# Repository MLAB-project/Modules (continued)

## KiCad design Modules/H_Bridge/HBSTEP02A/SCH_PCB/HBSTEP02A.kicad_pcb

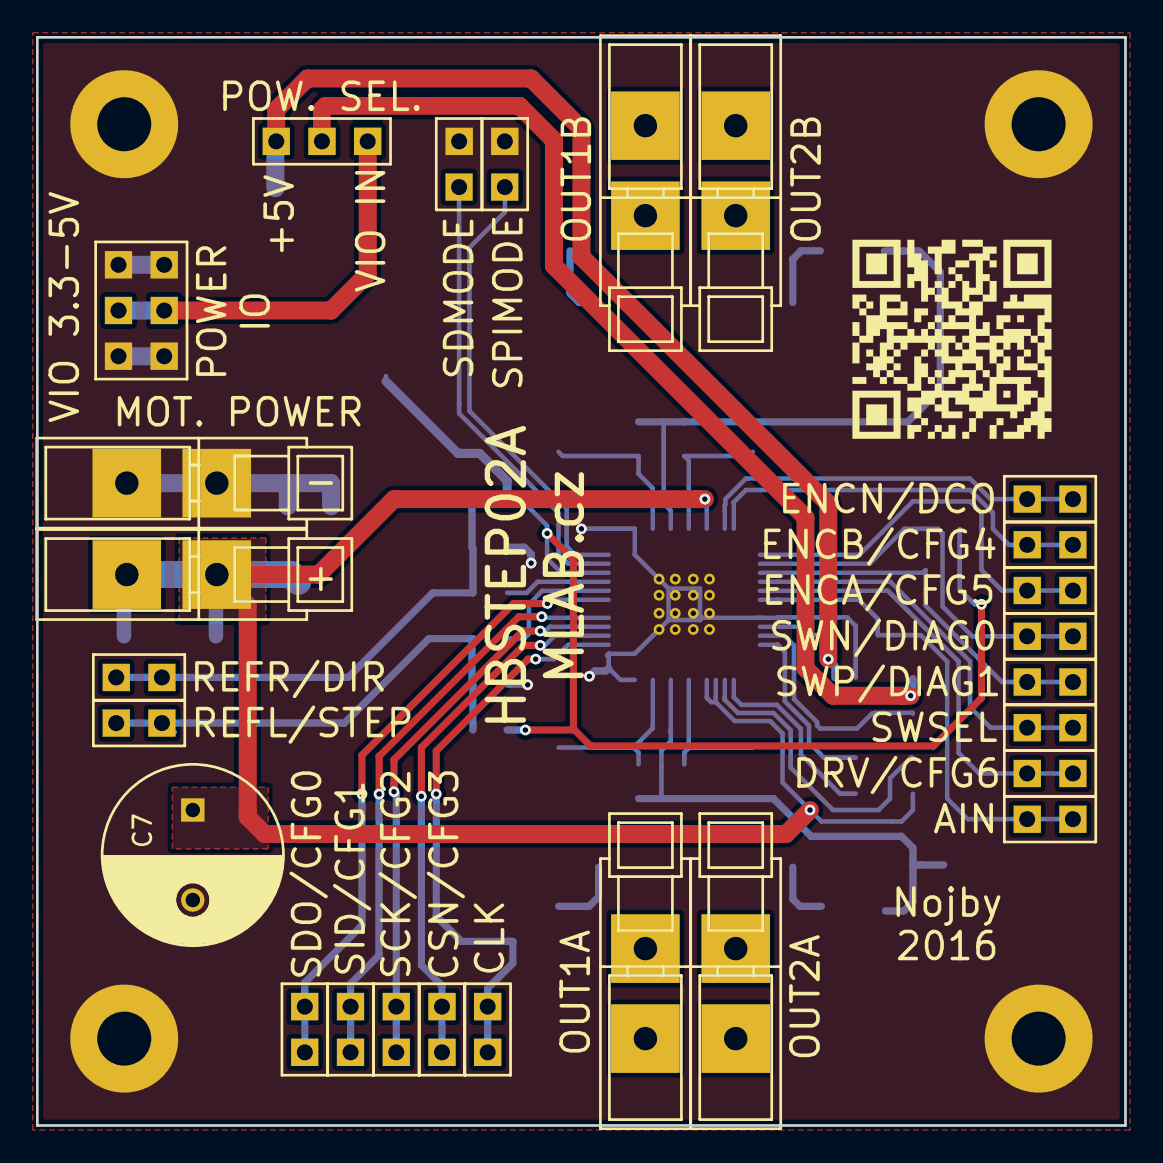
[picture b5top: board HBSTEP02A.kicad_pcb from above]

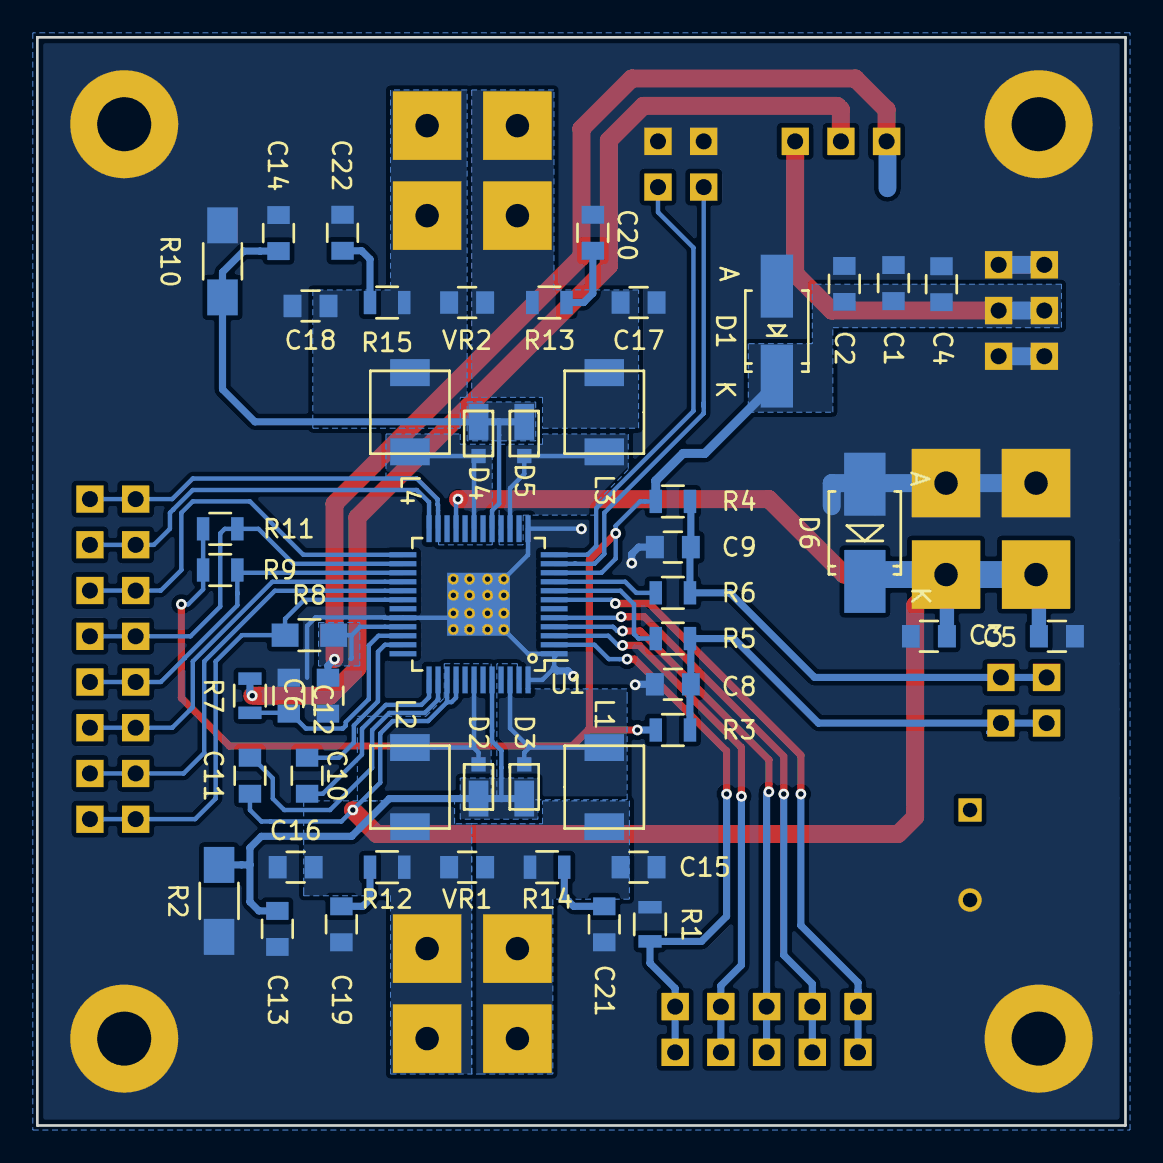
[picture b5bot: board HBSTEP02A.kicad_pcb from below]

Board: 2 copper layers, 60.5 x 60.5 mm, 79 parts (49 on the bottom side), 42 nets.

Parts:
C1, C6: 4u7; C_0805
C2, C3, C4, C5, C11, C13, C14: 100nF; C_0805
C7: 100uF/50V; C_Radial_D10_L13_P5
C8, C9: 1nF; C_0805
C10: 22n; C_0805
C12: 470nF; C_0805
C15, C16, C17, C18: 470pF; C_0805
C19, C20, C21, C22: 4n7; C_0805
D1: M4; SMA_Handsoldering
D2, D3, D4, D5: MSS1P6; SCHOT_D_MSS1P6
D6: M4; SMB_Handsoldering
J1: VIO 3.3-5V; Straight_2x03
J2: REFL/STEP; Straight_1x02
J3: REFR/DIR; Straight_1x02
J4: CLK; Straight_1x02
J5, J6, J16, J17, J24, J25: CONN1_1; WAGO256
J7: CSN/CFG3; Straight_1x02
J8: SCK/CFG2; Straight_1x02
J9: SID/CFG1; Straight_1x02
J10: SDO/CFG0; Straight_1x02
J11: ENCN/DCO; Straight_1x02
J12: ENCB/CFG4; Straight_1x02
J13: ENCA/CFG5; Straight_1x02
J14: SWP/DIAG1; Straight_1x02
J15: SWN/DIAG0; Straight_1x02
J18: POW. SEL.; Straight_1x03
J19: SDMODE; Straight_1x02
J20: DRV/CFG6; Straight_1x02
J21: SWSEL; Straight_1x02
J22: SPIMODE; Straight_1x02
J23: AIN; Straight_1x02
L1, L2, L3, L4: 100nH; Inductor_4.5_4.1
M1, M2, M3, M4: HOLE; MountingHole_3mm
R1: 1k; R_0805
R2, R10: 0R27; R_1206_HandSoldering
R3, R4, R9, R11: 10k; R_0805
R5, R6: 22k; R_0805
R7: 3.3; R_0805
R8: _R; R_0805_HandSoldering
R12, R13, R14, R15: 27; R_0805
U1: TMC5130A; TQFP-48-1EP_7x7mm_Pitch0.5mm_TRINAMIC
VR1, VR2: VR; C_0805

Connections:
+5V: C6.1, J18.1, R8.1, U1.33
GNDA: C1.2, C2.2, C3.2, C4.2, C5.2, C6.2, C7.2, C8.2, C9.2, C12.2, C13.2, C14.2, C15.1, C16.2, C17.1, C18.1, C19.2, C20.1, C21.1, C22.1, D1.2, D6.2, J1.1, J1.2, J1.5, J1.6, J6.1, J19.1, J22.1, M1.1, M2.1, M3.1, M4.1, R1.2, R2.1, R10.1, U1.1, U1.13, U1.32, U1.48, U1.49
unnamed: C8.1, J2.1, J2.2, R3.2, R5.2
unnamed: C9.1, J3.1, J3.2, R4.2, R6.2
unnamed: C10.1, U1.35
unnamed: C10.2, U1.37
unnamed: C11.1, U1.38
unnamed: C12.1, R7.2, U1.34
unnamed: C13.1, D2.2, D3.2, R2.2, U1.44
unnamed: C14.1, D4.2, D5.2, R10.2, U1.17
unnamed: C15.2, J16.1, L1.2, R14.2, VR1.1
unnamed: C16.1, J17.1, L2.2, R12.1, VR1.2
unnamed: C17.2, J24.1, L3.2, R13.2, VR2.1
unnamed: C18.2, J25.1, L4.2, R15.2, VR2.2
unnamed: C19.1, R12.2
unnamed: C20.2, R13.1
unnamed: C21.2, R14.1
unnamed: C22.2, R15.1
unnamed: D2.1, L2.1, U1.42
unnamed: D3.1, L1.1, U1.46
unnamed: D4.1, L4.1, U1.19
unnamed: D5.1, L3.1, U1.15
unnamed: J4.1, J4.2, R1.1, U1.2
unnamed: J7.1, J7.2, U1.3
unnamed: J8.1, J8.2, U1.4
unnamed: J9.1, J9.2, U1.5
unnamed: J10.1, J10.2, U1.7
unnamed: J11.1, J11.2, U1.23
unnamed: J12.1, J12.2, U1.24
unnamed: J13.1, J13.2, U1.25
unnamed: J14.1, J14.2, R9.2, U1.27
unnamed: J15.1, J15.2, R11.2, U1.26
unnamed: J19.2, U1.11
unnamed: J20.1, J20.2, U1.29
unnamed: J21.1, J21.2, U1.28
unnamed: J22.2, U1.12
unnamed: J23.1, J23.2, R8.2, U1.30
unnamed: R5.1, U1.8
unnamed: R6.1, U1.9
VCC: J18.2, R7.1
VCOM: C1.1, C2.1, C4.1, D1.1, J1.3, J1.4, J18.3, R3.1, R4.1, R9.1, R11.1, U1.10
VSS: C3.1, C5.1, C7.1, C11.2, D6.1, J5.1, U1.21, U1.39, U1.40

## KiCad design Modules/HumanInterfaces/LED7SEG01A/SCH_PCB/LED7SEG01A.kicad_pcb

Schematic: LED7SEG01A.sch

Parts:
AFF1: FYS-40011DS-11
C1: 10uF; SMD-0805
C2, C3: 47uF; TantalC_SizeC_Reflow
C4: 100nF; SMD-0805
D1: BZV55C-5,6V; MiniMELF_Standard
D2: M4; Diode-SMA_Standard
D3, D4: L-813ID; LED-10MM
J1, J27: JUMP_4X2; Straight_2x04
J5, J6, J7, J8, J9, J28, J29, J30, J31, J36: JUMP_2x1; Straight_2x01
J11, J12, J13, J14, J15, J16, J17, J18, J19, J20, J21, J22, J23, J24, J25, J26, J37, J38, J39, J40, J41, J42, J43, J44: CONN1_1; Straight_1x01
M1, M3, M5, M6, M7, M8, M9, M10: HOLE; MountingHole_3mm
R1, R2, R3, R4, R5, R6, R28, R30: 10k; SMD-0805
R7, R8, R9, R10, R11, R12, R13, R14, R25, R26, R27, R29, R31, R32: -; SMD-0805
R15, R16, R17, R18, R19, R20, R22: 150R; SMD-1206
R21: 300R; SMD-1206
R23: 0R; SMD-0805
R24: 0R; SMD-1206
U1: PCA9635PW; TSSOP28

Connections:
+12V: AFF1.1 (C.A.), AFF1.8 (C.A.), C3.1, D2.2 (K), D3.2, D4.2, J1.3 (4), J1.4, J1.5, J1.6 (5), J27.3 (4), J27.4, J27.5, J27.6 (5), J37.1, J38.1, J39.1, J40.1, J41.1, J42.1, J43.1, J44.1, R32.1
/#OE: J36.1, J36.2, R5.1, U1.23 (#OE)
/A: AFF1.7 (a), J21.1, R9.1, R17.1
/A0: R30.2, R31.1, U1.1 (A0)
/A1: R28.2, R29.1, U1.2 (A1)
/A2: R1.1, R25.2, U1.3 (A2)
/A3: R2.1, R26.2, U1.4 (A3)
/A4: R3.1, R27.2, U1.5 (A4)
/B: AFF1.6 (b), D4.1, J23.1, R11.1, R19.1
/C: AFF1.4 (c), J22.1, R10.1, R18.1
/D: AFF1.3 (d), J24.1, R12.1, R20.1
/DP: AFF1.5 (DP), J25.1, R13.1, R21.1
/E: D3.1, J26.1, R14.1, R22.1, R24.2
/F: AFF1.9 (f), J20.1, R8.1, R16.1
/G: AFF1.10 (g), J19.1, R7.1, R15.1
/LED00: J11.1, R7.2, R15.2, U1.6 (LED0)
/LED01: J12.1, R8.2, R16.2, U1.7 (LED1)
/LED02: J13.1, R9.2, R17.2, U1.8 (LED2)
/LED03: J14.1, R11.2, R19.2, U1.9 (LED3)
/LED04: J15.1, R13.2, R21.2, U1.10 (LED4)
/LED05: J16.1, R10.2, R18.2, U1.11 (LED5)
/LED06: J17.1, R12.2, R20.2, U1.12 (LED6)
/LED07: J18.1, R14.2, R22.2, U1.13 (LED7)
/SCL: J7.1, J7.2, J30.1, J30.2, R6.2, U1.26 (SCL)
/SDA: J6.1, J6.2, R4.2, R23.1, U1.27 (SDA)
GND: C1.2, C2.2, C3.2, C4.2, D1.1 (A), D2.1 (A), J1.1 (2), J1.2, J1.7 (8), J1.8, J8.1, J8.2, J9.1, J9.2, J27.1 (2), J27.2, J27.7 (8), J27.8, J31.1, J31.2, M1.1, M3.1, M5.1, M6.1, M7.1, M8.1, M9.1, M10.1, R1.2, R2.2, R3.2, R5.2, R29.2, R31.2, U1.14 (GND), U1.24 (A5), U1.25 (A6)
unnamed: AFF1.2 (e), R24.1
unnamed: J29.1, J29.2, R23.2
VDD: C1.1, C2.1, C4.1, D1.2 (K), J5.1, J5.2, J28.1, J28.2, R4.1, R6.1, R25.1, R26.1, R27.1, R28.1, R30.1, R32.2, U1.28 (VDD)

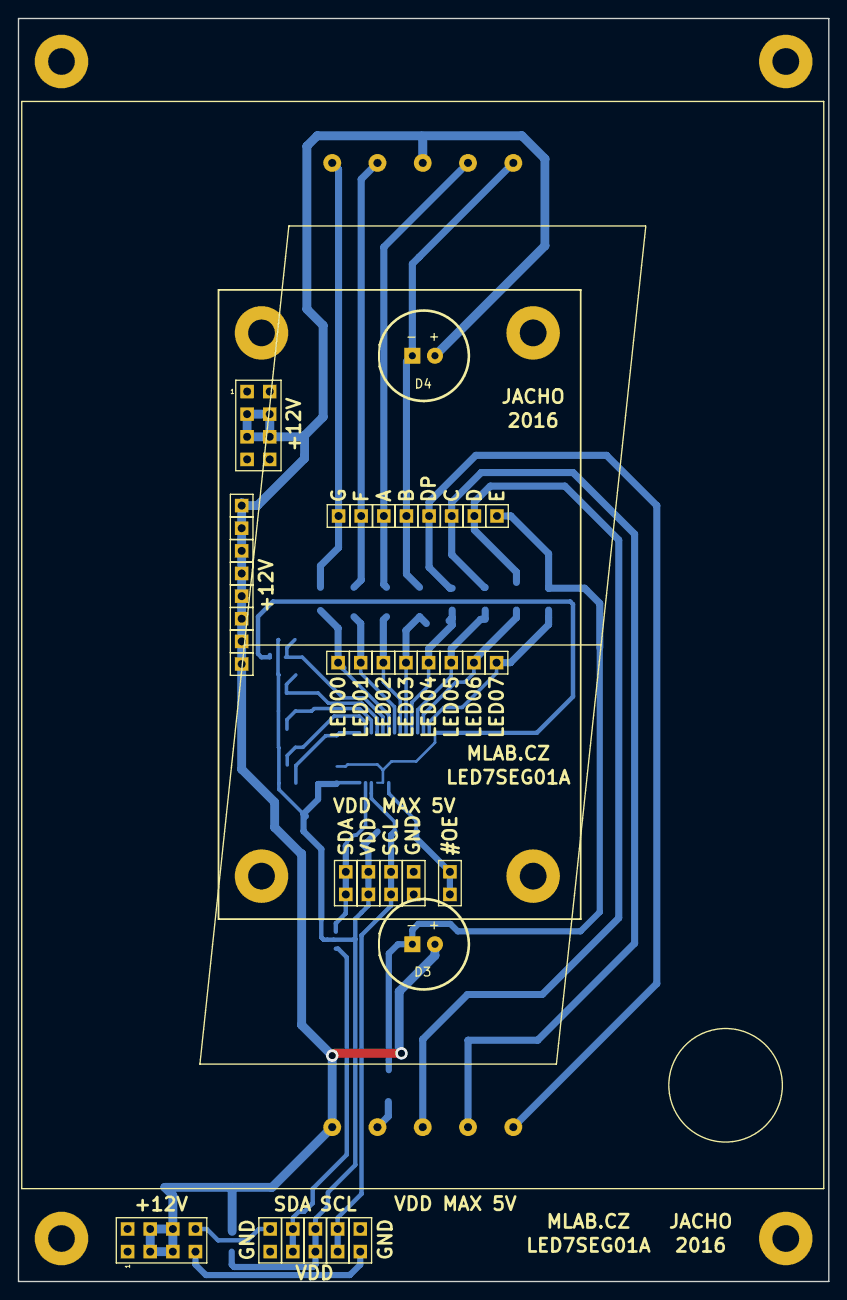
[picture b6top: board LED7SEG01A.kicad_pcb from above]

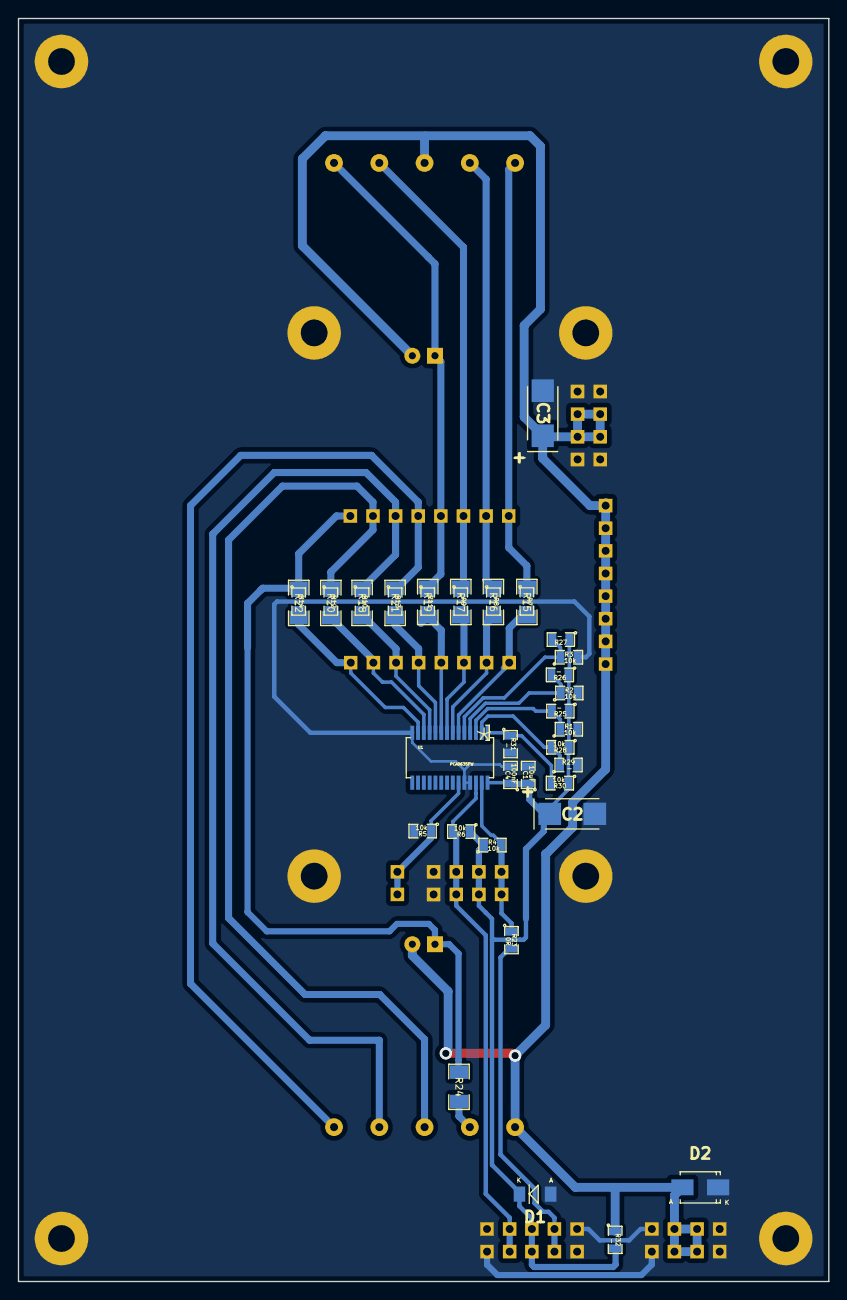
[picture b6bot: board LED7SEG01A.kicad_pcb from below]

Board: 2 copper layers, 90.9 x 141.7 mm, 86 parts (39 on the bottom side), 29 nets.

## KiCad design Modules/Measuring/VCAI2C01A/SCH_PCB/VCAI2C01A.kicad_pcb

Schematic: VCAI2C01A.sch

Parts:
C1, C4, C6, C7, C8, C9, C10, C11: C; SMD-0805
C2, C5, C12: 100nF; SMD-0805
C3: 10uF; SMD-0805
D1: BZV55C; Diode-MiniMELF_Standard
D2, D3, D4, D5, D6, D7, D8, D9: BAS85; MiniMELF_Standard
J2, J4, J6, J8: CONN_2; Straight_1x02
J3: JUMP_2x1; Straight_2x01
J5, J7, J9, J14, J15, J16, J17, J18, J19, J20, J21, J22, J23: JUMP_2x1; Straight_1x02
J10, J11: JUMP2_2x1; Straight_2x01
J13: JUMP_5X2; Straight_2x05
L1: BLM21PG300SN1D; SMD-0805
M1, M2, M3, M4: HOLE; MountingHole_3mm
R1, R2, R11, R12: 249R; SMD-1206
R3, R4, R5, R6, R13, R14, R15, R16: 180K; SMD-0805
R7, R8, R9, R10, R17, R18, R19, R20: 33K; SMD-0805
R21, R22, R23, R24: 10K; SMD-0805
U1, U2: TLC27L2ID; SOIC-8_3.9x4.9mm_Pitch1.27mm
U3: MCP3424; SOIC-14

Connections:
/A0: J10.1, R22.1, U3.9 (ADR0)
/A1: J11.1, R21.1, U3.10 (ADR1)
/IN1+: J9.1, J9.2, R1.1, R4.2
/IN1-: J2.1, J7.1, J7.2, R3.2
/IN1_2+: C1.1, D4.2 (A), R4.1, R7.2, U1.3 (+)
/IN1_2-: C6.2, D2.2 (A), R3.1, R9.1, U1.2 (-)
/IN2+: J16.1, J16.2, R2.1, R6.2
/IN2-: J4.1, J15.1, J15.2, R5.2
/IN2_2+: C4.1, D5.2 (A), R6.1, R8.2, U1.5 (+)
/IN2_2-: C7.2, D3.2 (A), R5.1, R10.1, U1.6 (-)
/IN3+: J19.1, J19.2, R11.1, R14.2
/IN3-: J6.1, J18.1, J18.2, R13.2
/IN3_2+: C8.1, D8.2 (A), R14.1, R17.2, U2.3 (+)
/IN3_2-: C10.2, D6.2 (A), R13.1, R19.1, U2.2 (-)
/IN4+: J22.1, J22.2, R12.1, R16.2
/IN4-: J8.1, J21.1, J21.2, R15.2
/IN4_2+: C9.1, D9.2 (A), R16.1, R18.2, U2.5 (+)
/IN4_2-: C11.2, D7.2 (A), R15.1, R20.1, U2.6 (-)
/OUT1: C6.1, R9.2, U1.1, U3.1 (CH1+)
/OUT2: C7.1, R10.2, U1.7, U3.3 (CH2+)
/OUT3: C10.1, R19.2, U2.1, U3.11 (CH3+)
/OUT4: C11.1, R20.2, U2.7, U3.13 (CH4+)
/SCL: J13.7, J13.8 (7), R24.2, U3.8 (SCL)
/SDA: J13.3 (4), J13.4, R23.2, U3.7 (SDA)
GND: C1.2, C2.2, C3.2, C4.2, C5.2, C8.2, C9.2, C12.2, D1.1 (K), J3.1, J3.2, J5.1, J5.2, J13.1 (2), J13.2, J13.9 (10), J13.10, J14.1, J14.2, J17.1, J17.2, J20.1, J20.2, J23.1, J23.2, M1.1, M2.1, M3.1, M4.1, R7.1, R8.1, R17.1, R18.1, R21.2, R22.2, U1.4 (GND), U2.4 (GND), U3.2 (CH1-), U3.4 (CH2-), U3.5 (VSS), U3.12 (CH3-), U3.14 (CH4-)
unnamed: C2.1, C3.1, L1.2, U3.6 (VDD)
unnamed: J2.2 (PM), R1.2
unnamed: J4.2 (PM), R2.2
unnamed: J6.2 (PM), R11.2
unnamed: J8.2 (PM), R12.2
VCC: C5.1, C12.1, D1.2 (A), D2.1 (K), D3.1 (K), D4.1 (K), D5.1 (K), D6.1 (K), D7.1 (K), D8.1 (K), D9.1 (K), J10.2, J11.2, J13.5 (6), J13.6, L1.1, R23.1, R24.1, U1.8 (VDD), U2.8 (VDD)

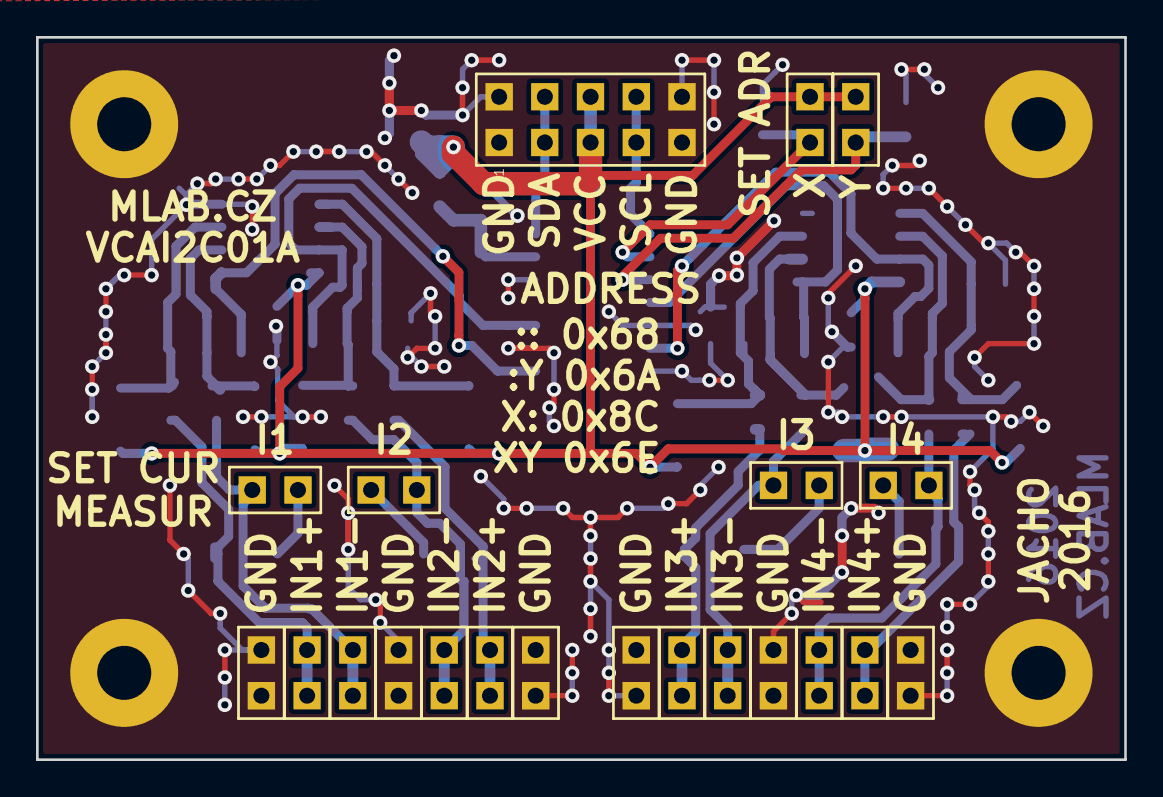
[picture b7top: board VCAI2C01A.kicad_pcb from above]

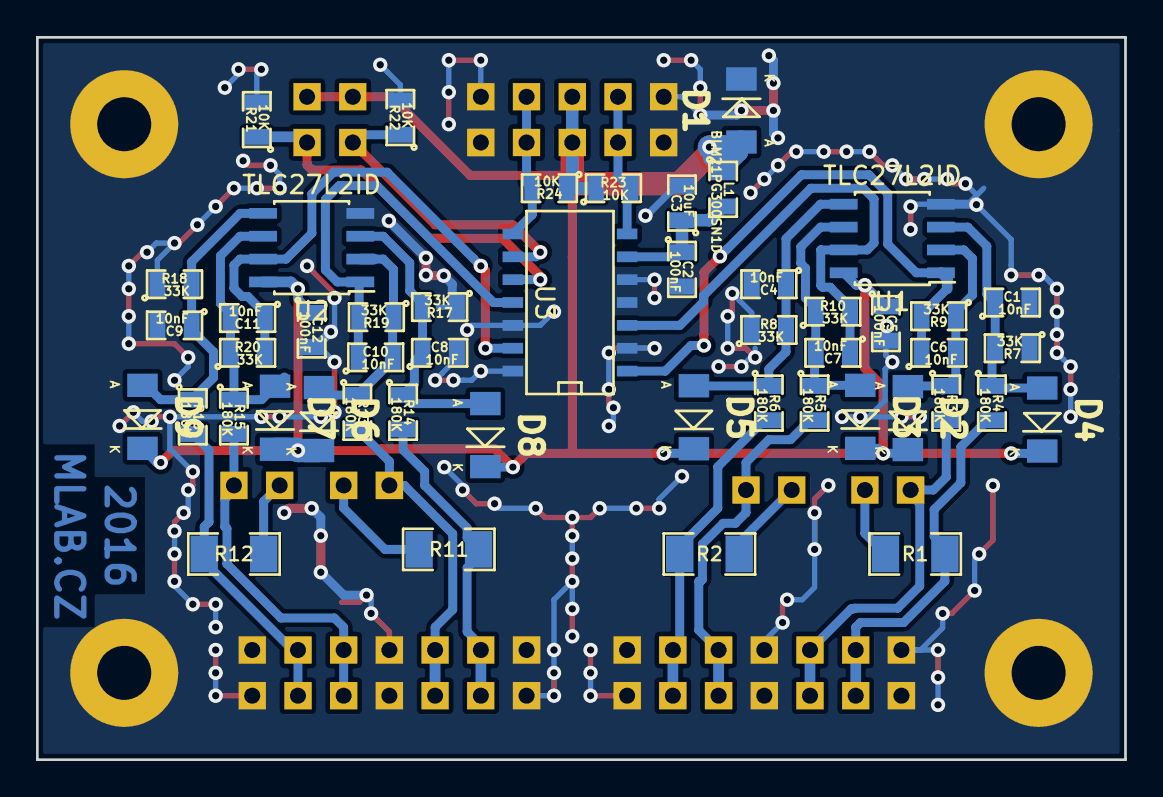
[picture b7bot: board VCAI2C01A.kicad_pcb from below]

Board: 2 copper layers, 60.5 x 40.1 mm, 74 parts (49 on the bottom side), 31 nets.

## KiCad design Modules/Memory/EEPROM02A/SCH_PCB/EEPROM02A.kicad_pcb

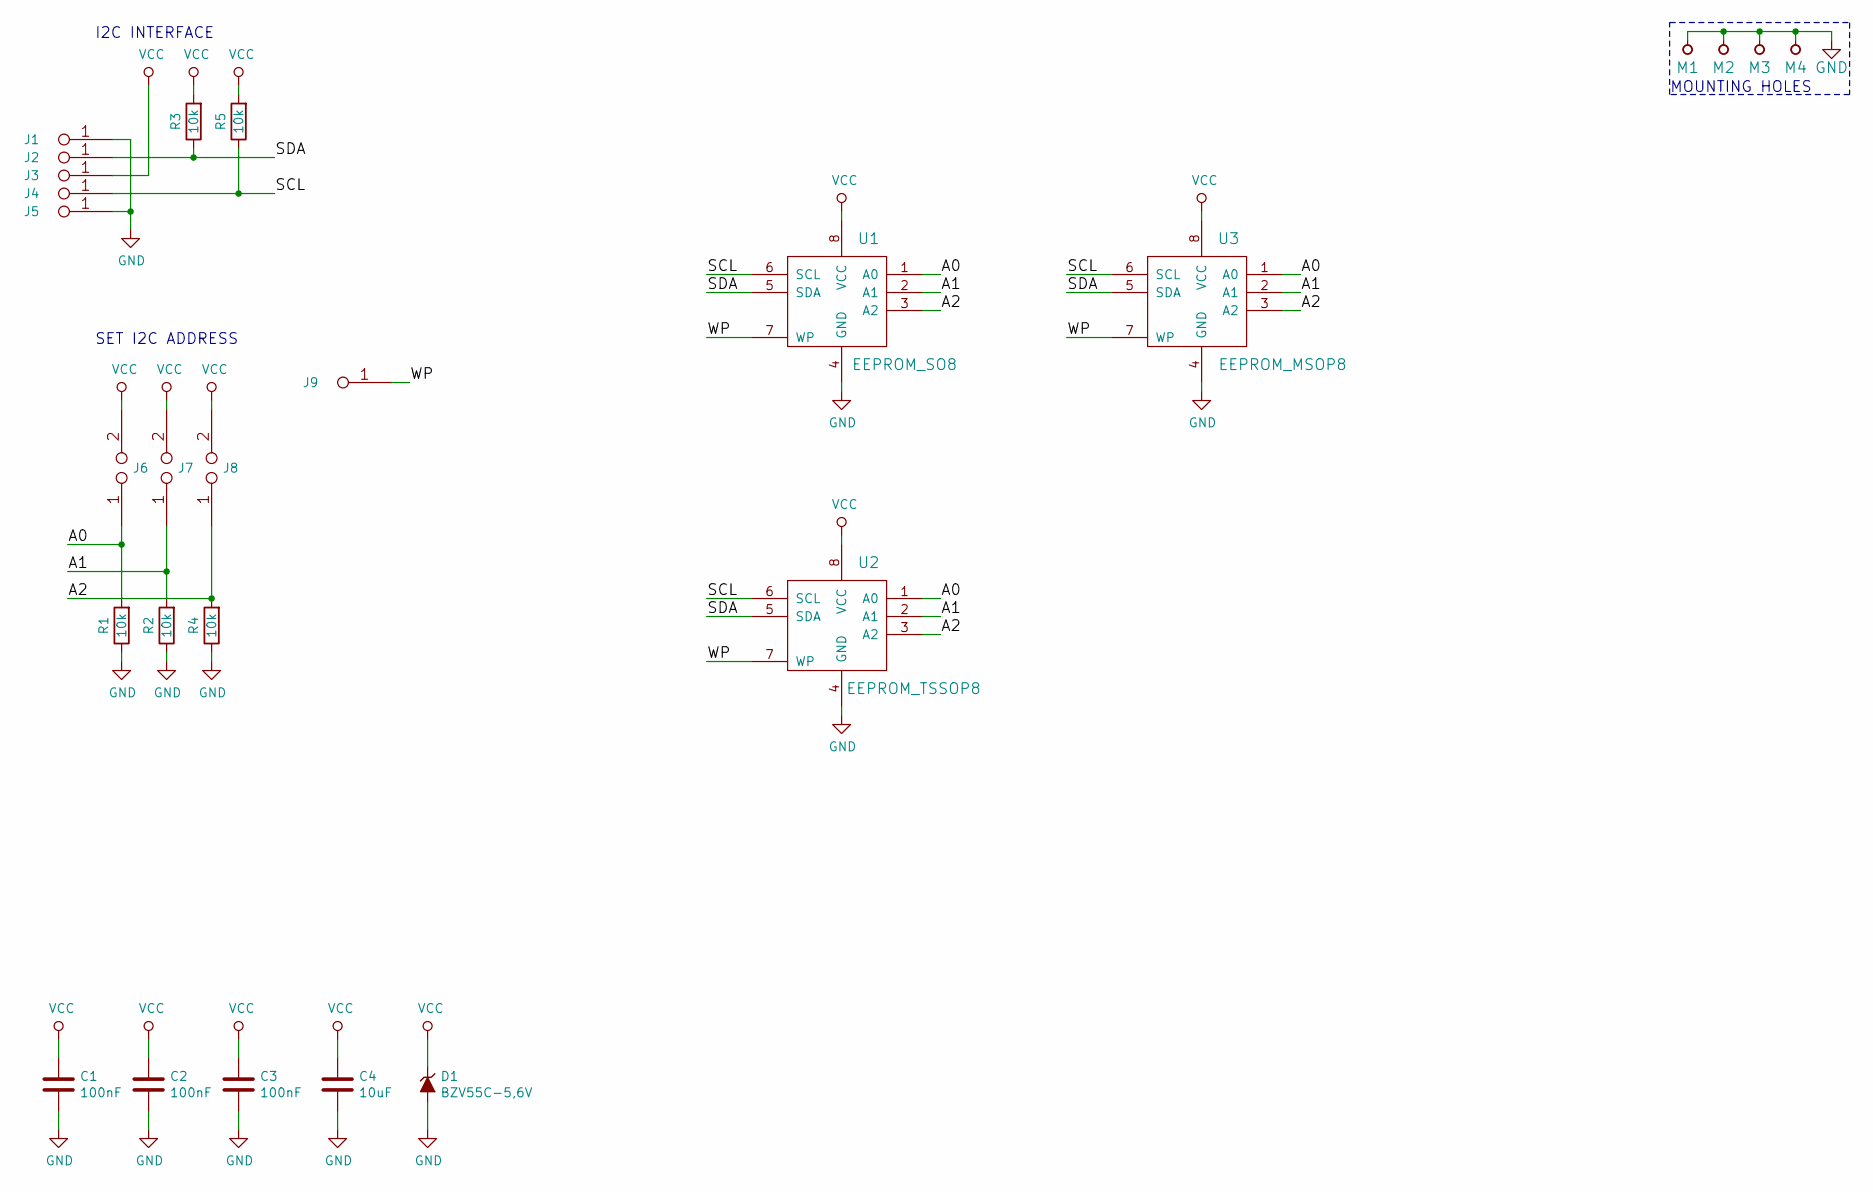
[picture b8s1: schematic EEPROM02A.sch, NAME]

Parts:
C1, C2, C3: 100nF; SMD-0805
C4: 10uF; SMD-0805
D1: BZV55C-5,6V; Diode-MiniMELF_Standard
J1, J2, J3, J4, J5, J9: JUMP_2x1; Straight_2x01
J6, J7, J8: JUMP2_2x1; Straight_2x01
M1, M2, M3, M4: HOLE; MountingHole_3mm
R1, R2, R3, R4, R5: 10k; SMD-0805
U1: EEPROM_SO8; SO-8
U2: EEPROM_TSSOP8; TSSOP-8_4.4x3mm_Pitch0.65mm
U3: EEPROM_MSOP8; MSOP-8_3x3mm_Pitch0.65mm

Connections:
/A0: J6.1, R1.2, U1.1 (A0), U2.1 (A0), U3.1 (A0)
/A1: J7.1, R2.2, U1.2 (A1), U2.2 (A1), U3.2 (A1)
/A2: J8.1, R4.2, U1.3 (A2), U2.3 (A2), U3.3 (A2)
/SCL: J4.1, J4.2, R5.1, U1.6 (SCL), U2.6 (SCL), U3.6 (SCL)
/SDA: J2.1, J2.2, R3.1, U1.5 (SDA), U2.5 (SDA), U3.5 (SDA)
/WP: J9.1, J9.2, U1.7 (WP), U2.7 (WP), U3.7 (WP)
GND: C1.2, C2.2, C3.2, C4.2, D1.2 (A), J1.1, J1.2, J5.1, J5.2, M1.1, M2.1, M3.1, M4.1, R1.1, R2.1, R4.1, U1.4 (GND), U2.4 (GND), U3.4 (GND)
VCC: C1.1, C2.1, C3.1, C4.1, D1.1 (K), J3.1, J3.2, J6.2, J7.2, J8.2, R3.2, R5.2, U1.8 (VCC), U2.8 (VCC), U3.8 (VCC)

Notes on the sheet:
MOUNTING HOLES
I2C INTERFACE
SET I2C ADDRESS

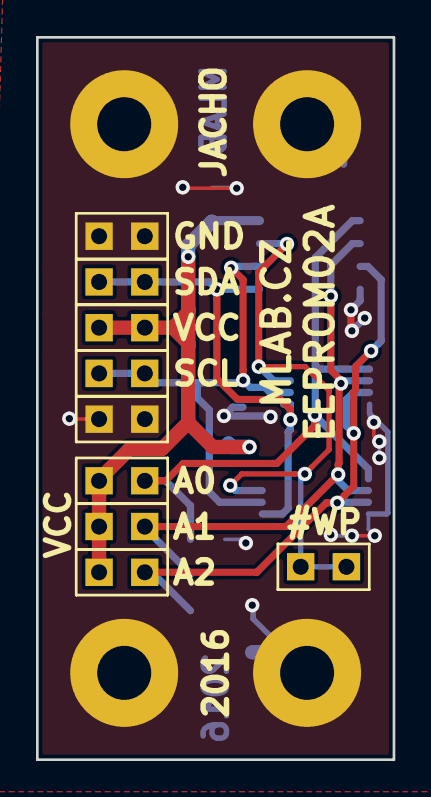
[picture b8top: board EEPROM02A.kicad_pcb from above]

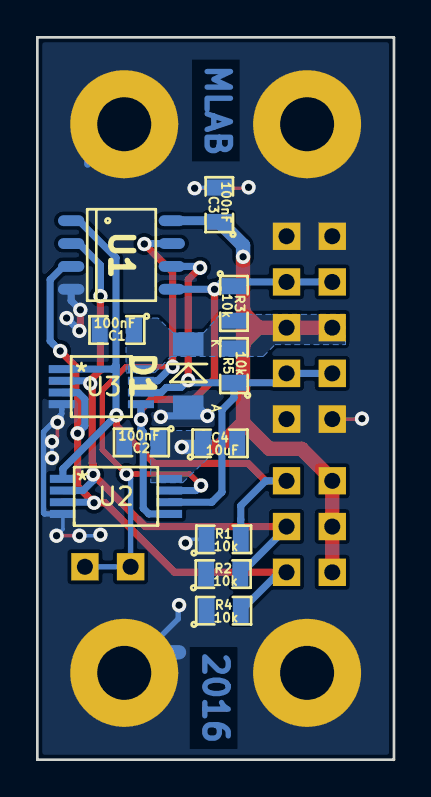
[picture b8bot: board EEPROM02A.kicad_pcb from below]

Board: 2 copper layers, 19.8 x 40.1 mm, 26 parts (13 on the bottom side), 8 nets.
